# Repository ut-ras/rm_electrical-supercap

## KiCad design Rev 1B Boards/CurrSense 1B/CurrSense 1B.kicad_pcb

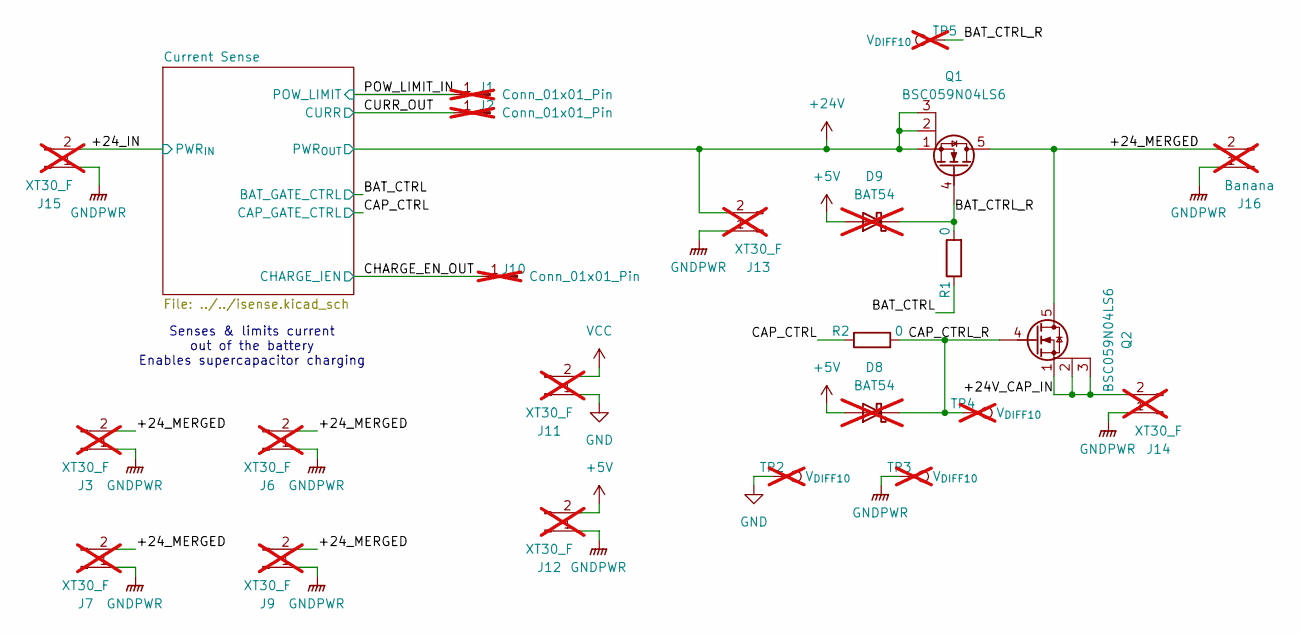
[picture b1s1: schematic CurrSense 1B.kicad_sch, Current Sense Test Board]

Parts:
D8, D9: BAT54; SOT-23_Handsoldering; Mouser Part Number 241-BAT54_R1_00001; not fitted
J1, J2, J10: Conn_01x01_Pin; SolderWire-2.5sqmm_1x01_D2.4mm_OD3.6mm; not fitted
J3, J6, J7, J9, J11, J12, J13, J14, J15: XT30_F; AMASS_XT30U-F_1x02_P5.0mm_Vertical; not fitted
J16: Banana; RM_Banana_Jack_2Pin; not fitted
Q1, Q2: BSC059N04LS6; Infineon_PG-TDSON-8_6.15x5.15mm; Mouser Part Number 726-BSC059N04LS6ATMA
R1, R2: 0; R_0603_1608Metric_Pad0.98x0.95mm_HandSolder; Mouser Part Number 660-RK73Z1JTTDD
TP2, TP3, TP4, TP5: V_{DIFF10}; TestPoint_Bridge_Pitch2.0mm_Drill0.7mm; not fitted

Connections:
+5V: D8.3 (A), D9.3 (A), J12.2
+24V: J13.2, Q1.1 (S), Q1.2 (S), Q1.3 (S); also elsewhere on the board
/+24V_CAP_IN: J14.2, Q2.1 (S), Q2.2 (S), Q2.3 (S)
/+24_IN: J15.2; also elsewhere on the board
/+24_MERGED: J3.2, J6.2, J7.2, J9.2, J16.2, Q1.5 (D), Q2.5 (D)
/BAT_CTRL: R1.1; also elsewhere on the board
/BAT_CTRL_R: D9.1 (K), Q1.4 (G), R1.2, TP5.1
/CAP_CTRL: R2.1; also elsewhere on the board
/CAP_CTRL_R: D8.1 (K), Q2.4 (G), R2.2, TP4.1
/CHARGE_EN_OUT: J10.1; also elsewhere on the board
/CURR_OUT: J2.1; also elsewhere on the board
/POW_LIMIT_IN: J1.1; also elsewhere on the board
GND: J11.1, TP2.1; also elsewhere on the board
GNDPWR: J3.1, J6.1, J7.1, J9.1, J12.1, J13.1, J14.1, J15.1, J16.1, TP3.1; also elsewhere on the board
VCC: J11.2; also elsewhere on the board

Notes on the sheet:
Senses & limits current out of the battery Enables supercapacitor charging

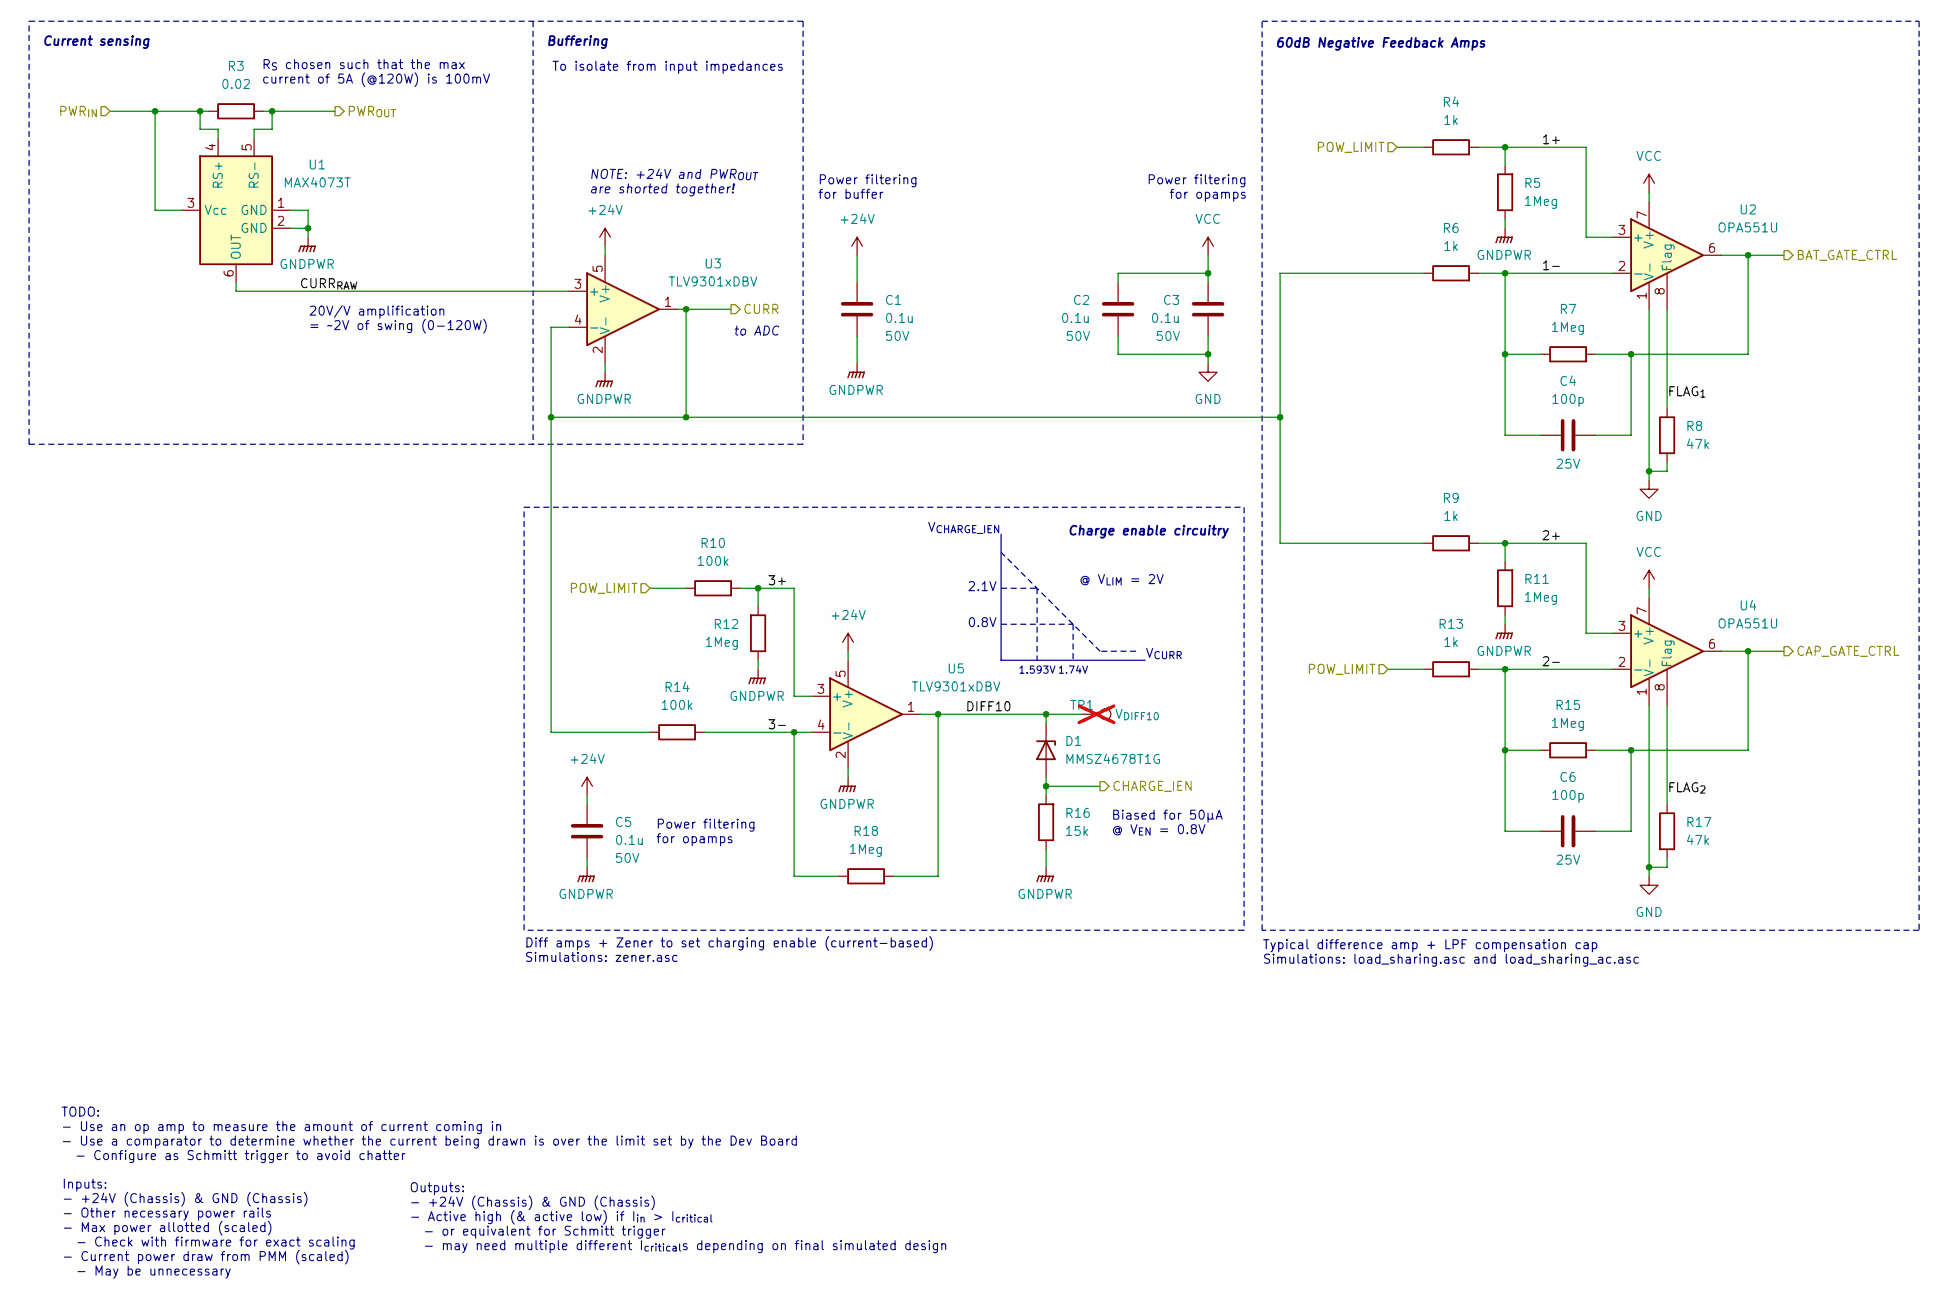
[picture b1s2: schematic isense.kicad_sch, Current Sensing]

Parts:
C1, C2, C3, C5: 0.1u; C_0603_1608Metric_Pad1.08x0.95mm_HandSolder; Voltage Rating 50V; Mouser Part Number 581-KGM15BR71H104JT
C4, C6: 100p; C_0603_1608Metric_Pad1.08x0.95mm_HandSolder; Voltage Rating 25V
D1: MMSZ4678T1G; D_SOD-123; Mouser Part Number 863-MMSZ4678T1G
R3: 0.02; R_0805_2012Metric_Pad1.20x1.40mm_HandSolder; Mouser Part Number 504-MFSA0805R0200FIM
R4, R6, R9, R13: 1k; R_0603_1608Metric_Pad0.98x0.95mm_HandSolder; Mouser Part Number 660-RN73R1JTD1001F50
R5, R7, R11, R12, R15, R18: 1Meg; R_0603_1608Metric_Pad0.98x0.95mm_HandSolder; Mouser Part Number 603-RC0603FR-071MP
R8, R17: 47k; R_0603_1608Metric_Pad0.98x0.95mm_HandSolder; Mouser Part Number 603-RC0603FR-1047KL
R10, R14: 100k; R_0603_1608Metric_Pad0.98x0.95mm_HandSolder; Mouser Part Number 660-RN73H1JTD1003D25
R16: 15k; R_0603_1608Metric_Pad0.98x0.95mm_HandSolder; Mouser Part Number 603-RT0603FRE1315KL
TP1: V_{DIFF10}; TestPoint_Bridge_Pitch2.0mm_Drill0.7mm; not fitted
U1: MAX4073T; SOT-23-6_Handsoldering; Mouser Part Number 700-MAX4073TAUT+T
U2, U4: OPA551U; SOIC-8_3.9x4.9mm_P1.27mm; Mouser Part Number 595-OPA551UA
U3, U5: TLV9301xDBV; SOT-23-5_HandSoldering; Mouser Part Number 595-TLV9301IDBVR

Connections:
+24V: C1.1, C5.1, R3.2, U1.5 (RS-), U3.5 (V+), U5.5 (V+); also elsewhere on the board
/+24_IN: R3.1, U1.3 (Vcc), U1.4 (RS+); also elsewhere on the board
/BAT_CTRL: C4.2, R7.2, U2.6; also elsewhere on the board
/CAP_CTRL: C6.2, R15.2, U4.6; also elsewhere on the board
/CHARGE_EN_OUT: D1.2 (A), R16.2; also elsewhere on the board
/CURR_OUT: R6.1, R9.1, R14.1, U3.1, U3.4 (-); also elsewhere on the board
/Current Sense/1+: R4.2, R5.2, U2.3 (+)
/Current Sense/1-: C4.1, R6.2, R7.1, U2.2 (-); also elsewhere on the board
/Current Sense/2+: R9.2, R11.2, U4.3 (+)
/Current Sense/2-: C6.1, R13.2, R15.1, U4.2 (-); also elsewhere on the board
/Current Sense/3+: R10.2, R12.2, U5.3 (+)
/Current Sense/3-: R14.2, R18.1, U5.4 (-); also elsewhere on the board
/Current Sense/CURR_{RAW}: U1.6 (OUT), U3.3 (+); also elsewhere on the board
/Current Sense/DIFF10: D1.1 (K), R18.2, TP1.1, U5.1; also elsewhere on the board
/Current Sense/FLAG_{1}: R8.1, U2.8 (Flag)
/Current Sense/FLAG_{2}: R17.1, U4.8 (Flag)
/POW_LIMIT_IN: R4.1, R10.1, R13.1; also elsewhere on the board
GND: C2.2, C3.2, R8.2, R17.2, U2.1 (V-), U2.4 (V-), U2.5 (V-), U4.1 (V-), U4.4 (V-), U4.5 (V-); also elsewhere on the board
GNDPWR: C1.2, C5.2, R5.1, R11.1, R12.1, R16.1, U1.1 (GND), U1.2 (GND), U3.2 (V-), U5.2 (V-); also elsewhere on the board
VCC: C2.1, C3.1, U2.7 (V+), U4.7 (V+); also elsewhere on the board

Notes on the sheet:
Inputs: - +24V (Chassis) & GND (Chassis) - Other necessary power rails - Max power allotted (scaled) - Check with firmware for exact scaling - Current power draw from PMM (scaled) - May be unnecessary
Power filtering for buffer
Power filtering for opamps
1.593V
Biased for 50µA @ V_{EN} = 0.8V
60dB Negative Feedback Amps
0.8V
1.74V
20V/V amplification = ~2V of swing (0-120W)
Typical difference amp + LPF compensation cap Simulations: load_sharing.asc and load_sharing_ac.asc
Diff amps + Zener to set charging enable (current-based) Simulations: zener.asc
Outputs: - +24V (Chassis) & GND (Chassis) - Active high (& active low) if I_{in} > I_{critical} - or equivalent for Schmitt trigger - may need multiple different I_{critical}s depending on final simulated design
V_{CHARGE_IEN}
V_{CURR}
R_{S} chosen such that the max current of 5A (@120W) is 100mV
TODO: - Use an op amp to measure the amount of current coming in - Use a comparator to determine whether the current being drawn is over the limit set by the Dev Board - Configure as Schmitt trigger to avoid chatter
2.1V
NOTE: +24V and PWR_{OUT} are shorted together!
To isolate from input impedances
Charge enable circuitry
to ADC
Buffering
Current sensing
@ V_{LIM} = 2V

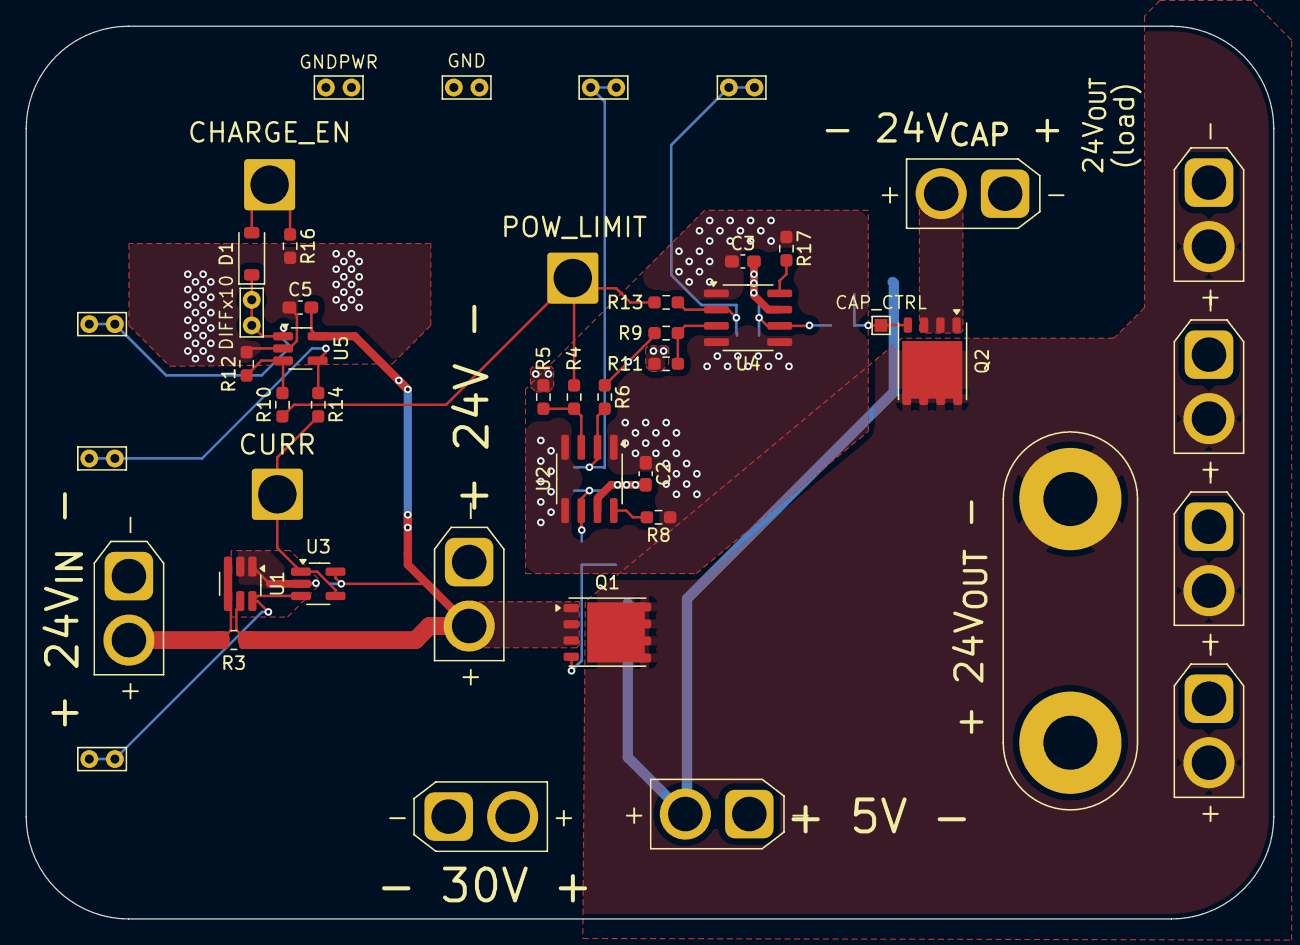
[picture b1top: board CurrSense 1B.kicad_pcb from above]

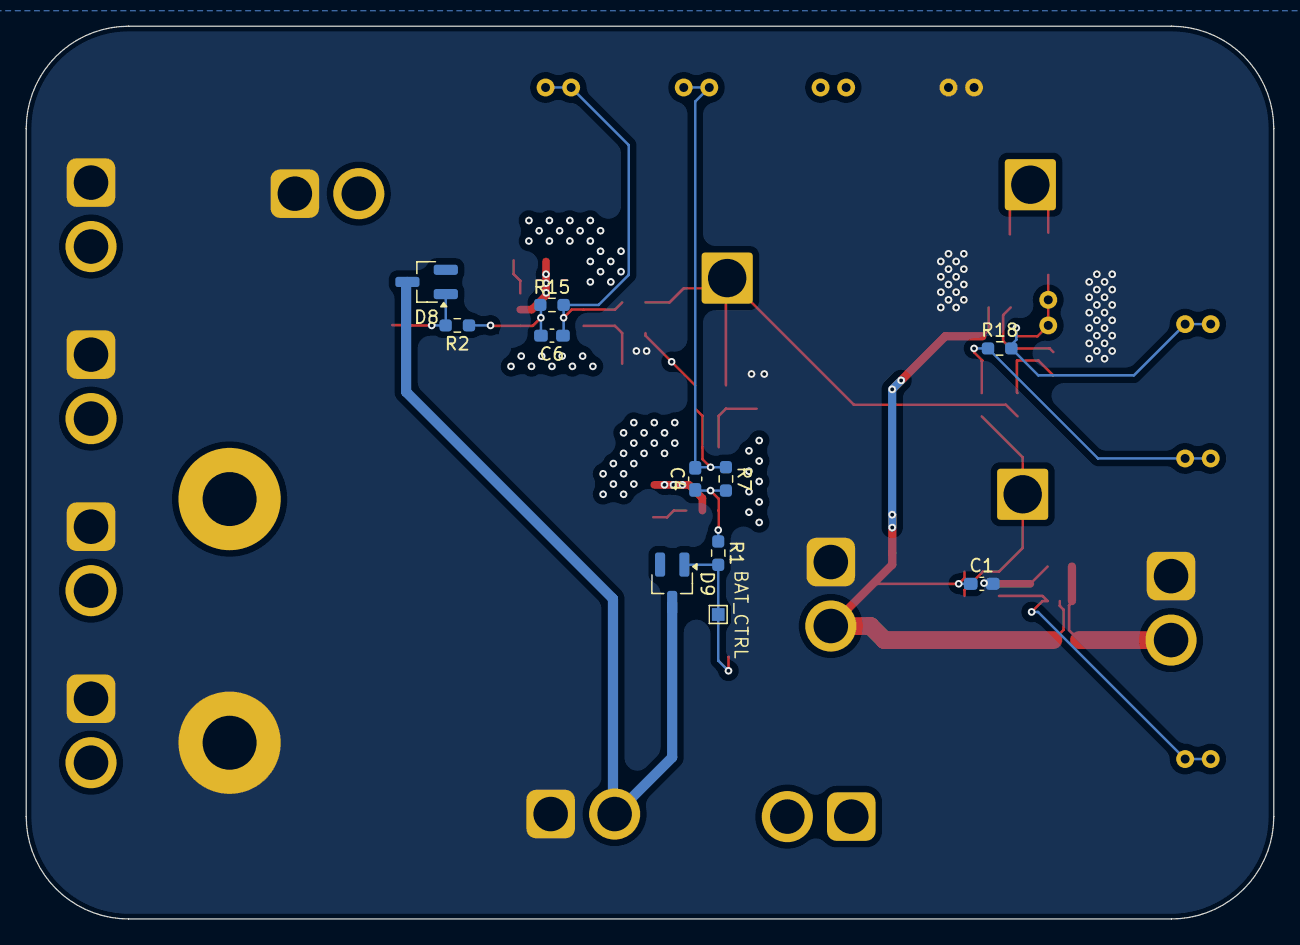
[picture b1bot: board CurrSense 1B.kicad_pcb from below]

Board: 4 copper layers, 97.5 x 69.8 mm, 57 parts (11 on the bottom side), 25 nets.

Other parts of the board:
TP6: CE_OUT; TestPoint_Bridge_Pitch2.0mm_Drill0.7mm
TP7: CE_IN_NEG; TestPoint_Bridge_Pitch2.0mm_Drill0.7mm
TP8: I_OUT; TestPoint_Bridge_Pitch2.0mm_Drill0.7mm
TP9: CAP_IN_NEG; TestPoint_Bridge_Pitch2.0mm_Drill0.7mm
TP10: BAT_IN_NEG; TestPoint_Bridge_Pitch2.0mm_Drill0.7mm

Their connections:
/Current Sense/1-: TP10.1; also elsewhere on the board
/Current Sense/2-: TP9.1; also elsewhere on the board
/Current Sense/3-: TP7.1; also elsewhere on the board
/Current Sense/CURR_{RAW}: TP8.1; also elsewhere on the board
/Current Sense/DIFF10: TP6.1; also elsewhere on the board

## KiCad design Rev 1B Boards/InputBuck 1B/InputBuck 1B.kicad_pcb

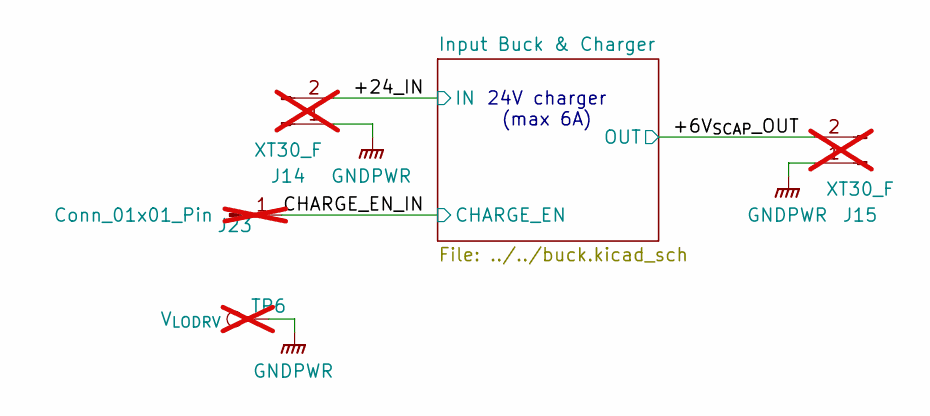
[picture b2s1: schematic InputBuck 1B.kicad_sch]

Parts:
J14, J15: XT30_F; AMASS_XT30U-F_1x02_P5.0mm_Vertical; not fitted
J23: Conn_01x01_Pin; SolderWire-2.5sqmm_1x01_D2.4mm_OD3.6mm; not fitted
TP6: V_{LODRV}; TestPoint_Bridge_Pitch2.0mm_Drill0.7mm; not fitted

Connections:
/+6V_{SCAP}_OUT: J15.2; also elsewhere on the board
/+24_IN: J14.2; also elsewhere on the board
/CHARGE_EN_IN: J23.1; also elsewhere on the board
GNDPWR: J14.1, J15.1, TP6.1; also elsewhere on the board

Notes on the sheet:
24V charger (max 6A)

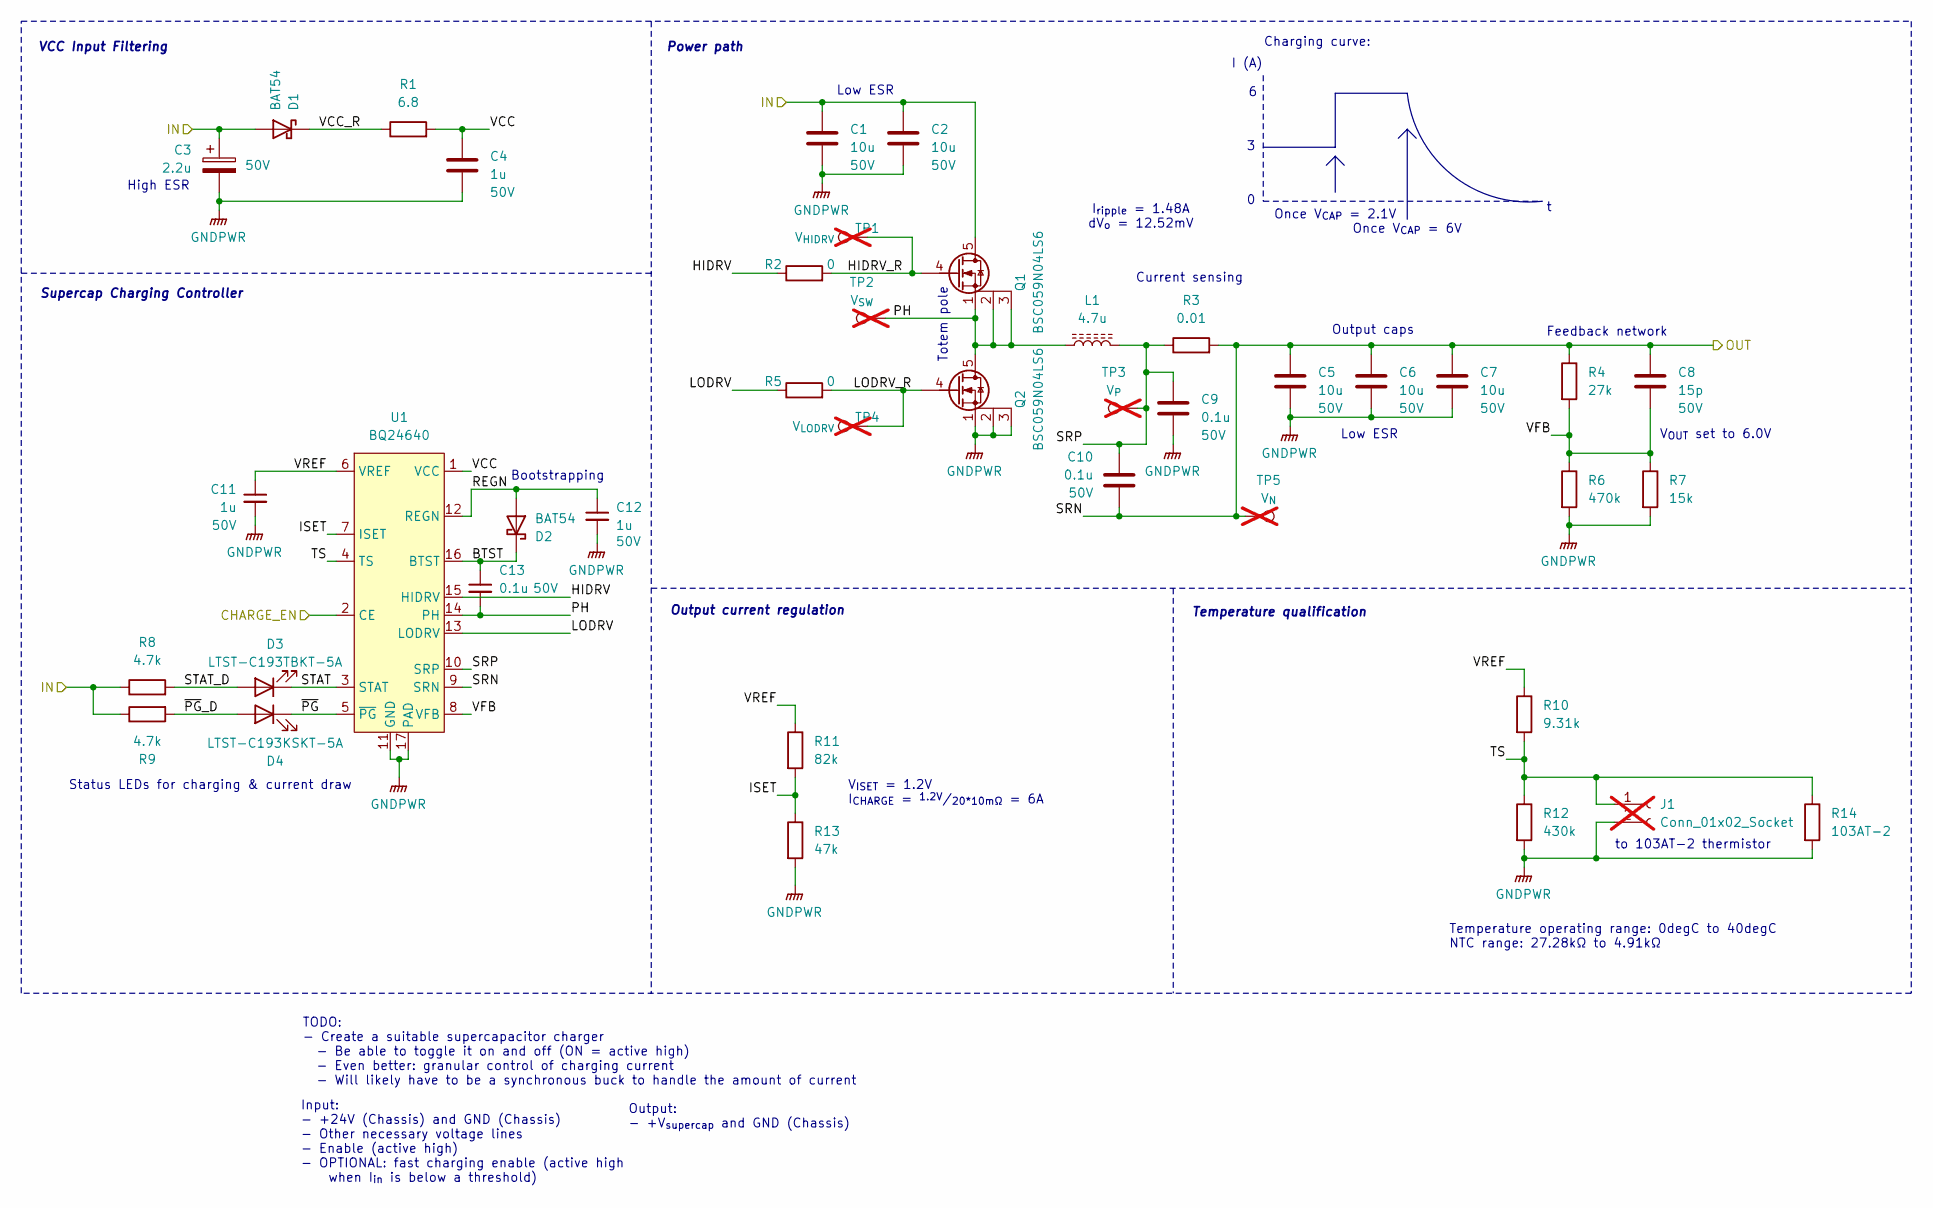
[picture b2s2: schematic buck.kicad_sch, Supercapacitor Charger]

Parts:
C1, C2, C5, C6, C7: 10u; C_1206_3216Metric_Pad1.33x1.80mm_HandSolder; Voltage Rating 50V; Mouser Part Number 187-CL31A106KBHNNNE
C3: 2.2u; C_Radial_D5.0mm_H11.0mm_P2.00mm; Voltage Rating 50V; Mouser Part Number 710-860010672006
C4, C11, C12: 1u; C_0603_1608Metric_Pad1.08x0.95mm_HandSolder; Voltage Rating 50V; Mouser Part Number 963-UMK107BJ105KA-T
C8: 15p; C_0603_1608Metric_Pad1.08x0.95mm_HandSolder; Voltage Rating 50V; Mouser Part Number 791-0603N150F500CT
C9, C10, C13: 0.1u; C_0603_1608Metric_Pad1.08x0.95mm_HandSolder; Voltage Rating 50V; Mouser Part Number 581-KGM15BR71H104JT
D1, D2: BAT54; SOT-23_Handsoldering; Mouser Part Number 241-BAT54_R1_00001
D3: LTST-C193TBKT-5A; LED_0603_1608Metric_Pad1.05x0.95mm_HandSolder; Mouser Part Number 859-LTSTC193TBKT5A
D4: LTST-C193KSKT-5A; LED_0603_1608Metric_Pad1.05x0.95mm_HandSolder; Mouser Part Number 859-LTSTC193KSKT5A
J1: Conn_01x02_Socket; PinSocket_1x02_P2.54mm_Vertical; not fitted
L1: 4.7u; L_Bourns_SRN8040TA; Mouser Part Number 652-SRN8040TA-4R7M
Q1, Q2: BSC059N04LS6; Infineon_PG-TDSON-8_6.15x5.15mm; Mouser Part Number 726-BSC059N04LS6ATMA
R1: 6.8; R_0805_2012Metric_Pad1.20x1.40mm_HandSolder; Mouser Part Number 660-RK73B2ATTD6R8J
R2, R5: 0; R_0603_1608Metric_Pad0.98x0.95mm_HandSolder; Mouser Part Number 660-RK73Z1JTTDD
R3: 0.01; R_0612_1632Metric_Pad1.18x3.40mm_HandSolder; Mouser Part Number 652-CFG0612FXR010ELF
R4: 27k; R_0603_1608Metric_Pad0.98x0.95mm_HandSolder; Mouser Part Number 660-RN73H1JTD2702B25
R6: 470k; R_0603_1608Metric_Pad0.98x0.95mm_HandSolder; Mouser Part Number 660-RN73R1JTD4703B25
R7: 15k; R_0603_1608Metric_Pad0.98x0.95mm_HandSolder; Mouser Part Number 603-RT0603FRE1315KL
R8, R9: 4.7k; R_0603_1608Metric_Pad0.98x0.95mm_HandSolder; Mouser Part Number 660-RN73R1JTD4701F50
R10: 9.31k; R_0603_1608Metric_Pad0.98x0.95mm_HandSolder; Mouser Part Number 603-RT0603DRE079K31L
R11: 82k; R_0603_1608Metric_Pad0.98x0.95mm_HandSolder; Mouser Part Number 603-RT0603FRE0782KL
R12: 430k; R_0603_1608Metric_Pad0.98x0.95mm_HandSolder; Mouser Part Number 603-RT0603FRE07430KL
R13: 47k; R_0603_1608Metric_Pad0.98x0.95mm_HandSolder; Mouser Part Number 603-RC0603FR-1047KL
R14: 103AT-2; Mouser Part Number 504-NRNE104H3435B2H
TP1: V_{HIDRV}; TestPoint_Bridge_Pitch2.0mm_Drill0.7mm; not fitted
TP2: V_{SW}; TestPoint_Bridge_Pitch2.0mm_Drill0.7mm; not fitted
TP3: V_{P}; TestPoint_Bridge_Pitch2.0mm_Drill0.7mm; not fitted
TP4: V_{LODRV}; TestPoint_Bridge_Pitch2.0mm_Drill0.7mm; not fitted
TP5: V_{N}; TestPoint_Bridge_Pitch2.0mm_Drill0.7mm; not fitted
U1: BQ24640; QFN50P350X350X100-17N-D; Mouser Part Number 595-BQ24640RVAR

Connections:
/+6V_{SCAP}_OUT: C5.1, C6.1, C7.1, C8.1, C10.2, R3.2, R4.1, TP5.1, U1.9 (SRN); also elsewhere on the board
/+24_IN: C1.1, C2.1, C3.1, D1.1 (A), Q1.5 (D), R8.1, R9.1; also elsewhere on the board
/CHARGE_EN_IN: U1.2 (CE); also elsewhere on the board
/Input Buck & Charger/BTST: C13.1, D2.3 (K), U1.16 (BTST)
/Input Buck & Charger/HIDRV: R2.1, U1.15 (HIDRV)
/Input Buck & Charger/HIDRV_R: Q1.4 (G), R2.2, TP1.1
/Input Buck & Charger/ISET: R11.2, R13.1, U1.7 (ISET)
/Input Buck & Charger/LODRV: R5.1, U1.13 (LODRV)
/Input Buck & Charger/LODRV_R: Q2.4 (G), R5.2, TP4.1
/Input Buck & Charger/PH: C13.2, L1.1, Q1.1 (S), Q1.2 (S), Q1.3 (S), Q2.5 (D), TP2.1, U1.14 (PH)
/Input Buck & Charger/REGN: C12.1, D2.1 (A), U1.12 (REGN)
/Input Buck & Charger/SRP: C9.1, C10.1, L1.2, R3.1, TP3.1, U1.10 (SRP)
/Input Buck & Charger/STAT: D3.1 (K), U1.3 (STAT)
/Input Buck & Charger/STAT_D: D3.2 (A), R8.2
/Input Buck & Charger/TS: J1.1, R10.2, R12.1, U1.4 (TS)
/Input Buck & Charger/VCC: C4.1, R1.2, U1.1 (VCC)
/Input Buck & Charger/VCC_R: D1.3 (K), R1.1
/Input Buck & Charger/VFB: C8.2, R4.2, R6.1, R7.1, U1.8 (VFB)
/Input Buck & Charger/VREF: C11.1, R10.1, R11.1, U1.6 (VREF)
/Input Buck & Charger/~PG: D4.1 (K), U1.5 (~PG)
/Input Buck & Charger/~PG_D: D4.2 (A), R9.2
GNDPWR: C1.2, C2.2, C3.2, C4.2, C5.2, C6.2, C7.2, C9.2, C11.2, C12.2, J1.2, Q2.1 (S), Q2.2 (S), Q2.3 (S), R6.2, R7.2, R12.2, R13.2, U1.11 (GND), U1.17 (PAD); also elsewhere on the board

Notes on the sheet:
Charging curve:
Current sensing
Once V_{CAP} = 6V
Totem pole
to 103AT-2 thermistor
TODO: - Create a suitable supercapacitor charger - Be able to toggle it on and off (ON = active high) - Even better: granular control of charging current - Will likely have to be a synchronous buck to handle the amount of current
Status LEDs for charging & current draw
Low ESR
V_{OUT} set to 6.0V
Temperature qualification
I_{ripple} = 1.48A dV_{o} = 12.52mV
Output caps
Bootstrapping
V_{ISET} = 1.2V I_{CHARGE} = ^{1.2V}/_{20*10mΩ} = 6A
Once V_{CAP} = 2.1V
Input: - +24V (Chassis) and GND (Chassis) - Other necessary voltage lines - Enable (active high) - OPTIONAL: fast charging enable (active high when I_{in} is below a threshold)
High ESR
Feedback network
Output: - +V_{supercap} and GND (Chassis)
Power path
Supercap Charging Controller
VCC Input Filtering
Temperature operating range: 0degC to 40degC NTC range: 27.28kΩ to 4.91kΩ
I (A)
Output current regulation

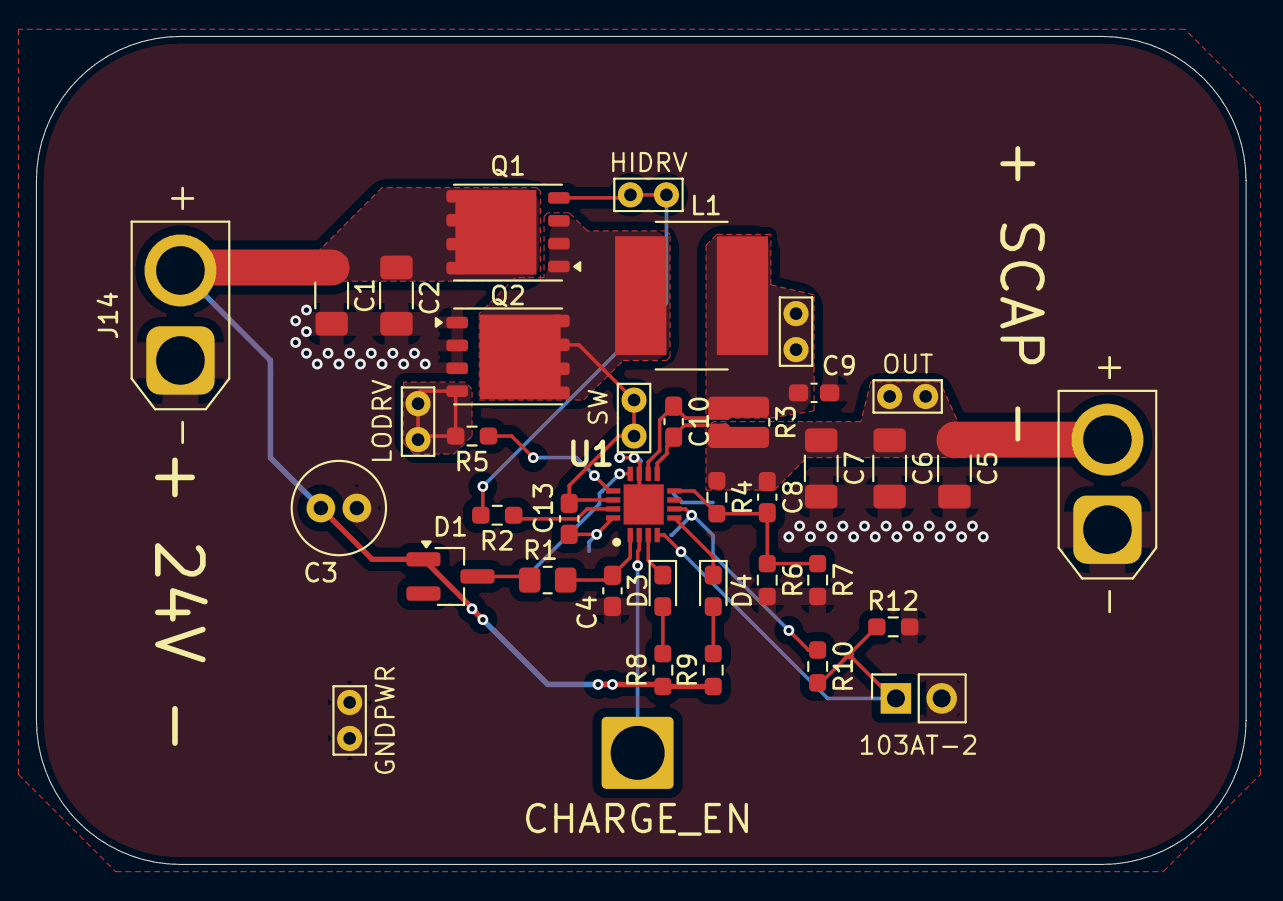
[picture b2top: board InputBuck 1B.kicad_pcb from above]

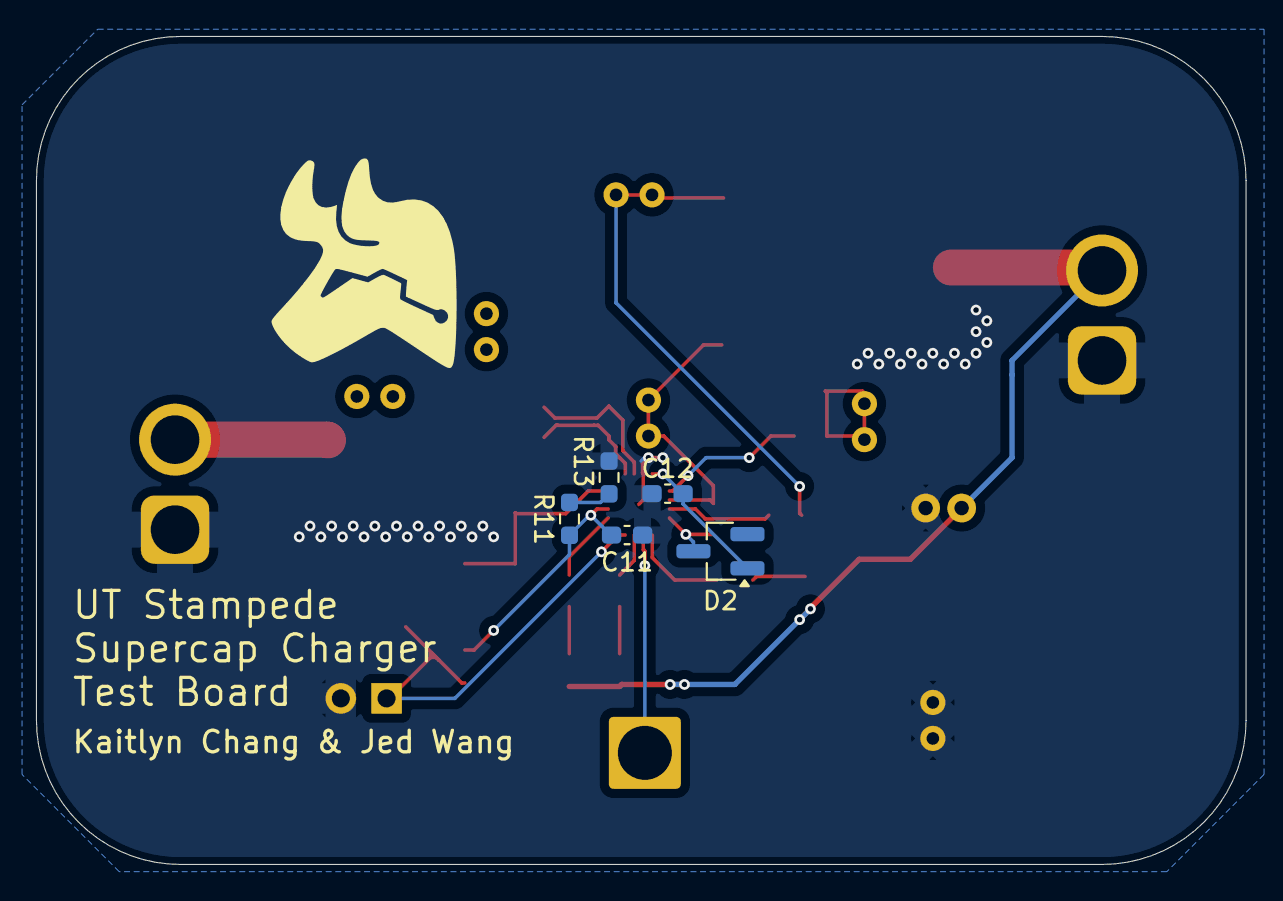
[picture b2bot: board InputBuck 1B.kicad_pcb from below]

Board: 4 copper layers, 67.2 x 46.0 mm, 44 parts (5 on the bottom side), 22 nets.

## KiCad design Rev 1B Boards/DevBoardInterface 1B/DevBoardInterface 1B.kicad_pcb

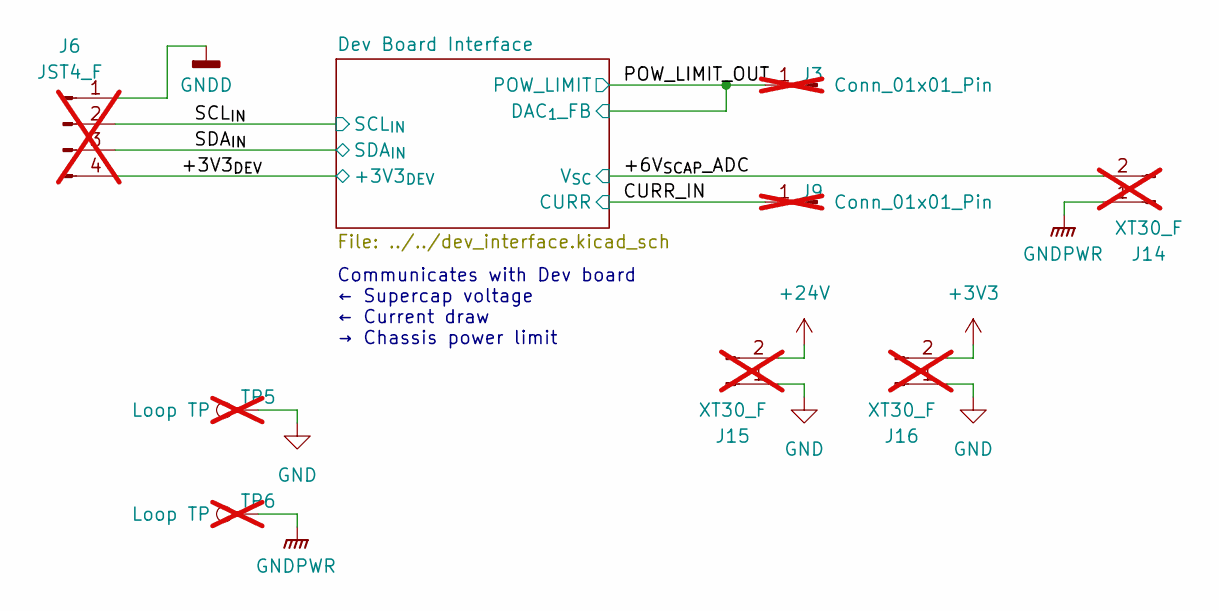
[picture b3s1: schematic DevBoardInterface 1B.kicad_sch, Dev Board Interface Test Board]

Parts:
J3, J9: Conn_01x01_Pin; SolderWire-2.5sqmm_1x01_D2.4mm_OD3.6mm; not fitted
J6: JST4_F; JST_GH_BM04B-GHS-TBT_1x04-1MP_P1.25mm_Vertical; not fitted
J14, J15, J16: XT30_F; AMASS_XT30U-F_1x02_P5.0mm_Vertical; not fitted
TP5, TP6: Loop TP; TestPoint_Bridge_Pitch2.0mm_Drill0.7mm; not fitted

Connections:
+3V3: J16.2; also elsewhere on the board
+24V: J15.2; also elsewhere on the board
/+3V3_{DEV}: J6.4; also elsewhere on the board
/+6V_{SCAP}_ADC: J14.2; also elsewhere on the board
/CURR_IN: J9.1; also elsewhere on the board
/POW_LIMIT_OUT: J3.1; also elsewhere on the board
/SCL_{IN}: J6.2; also elsewhere on the board
/SDA_{IN}: J6.3; also elsewhere on the board
GND: J15.1, J16.1, TP5.1; also elsewhere on the board
GNDD: J6.1; also elsewhere on the board
GNDPWR: J14.1, TP6.1; also elsewhere on the board

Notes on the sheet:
Communicates with Dev board ← Supercap voltage ← Current draw → Chassis power limit

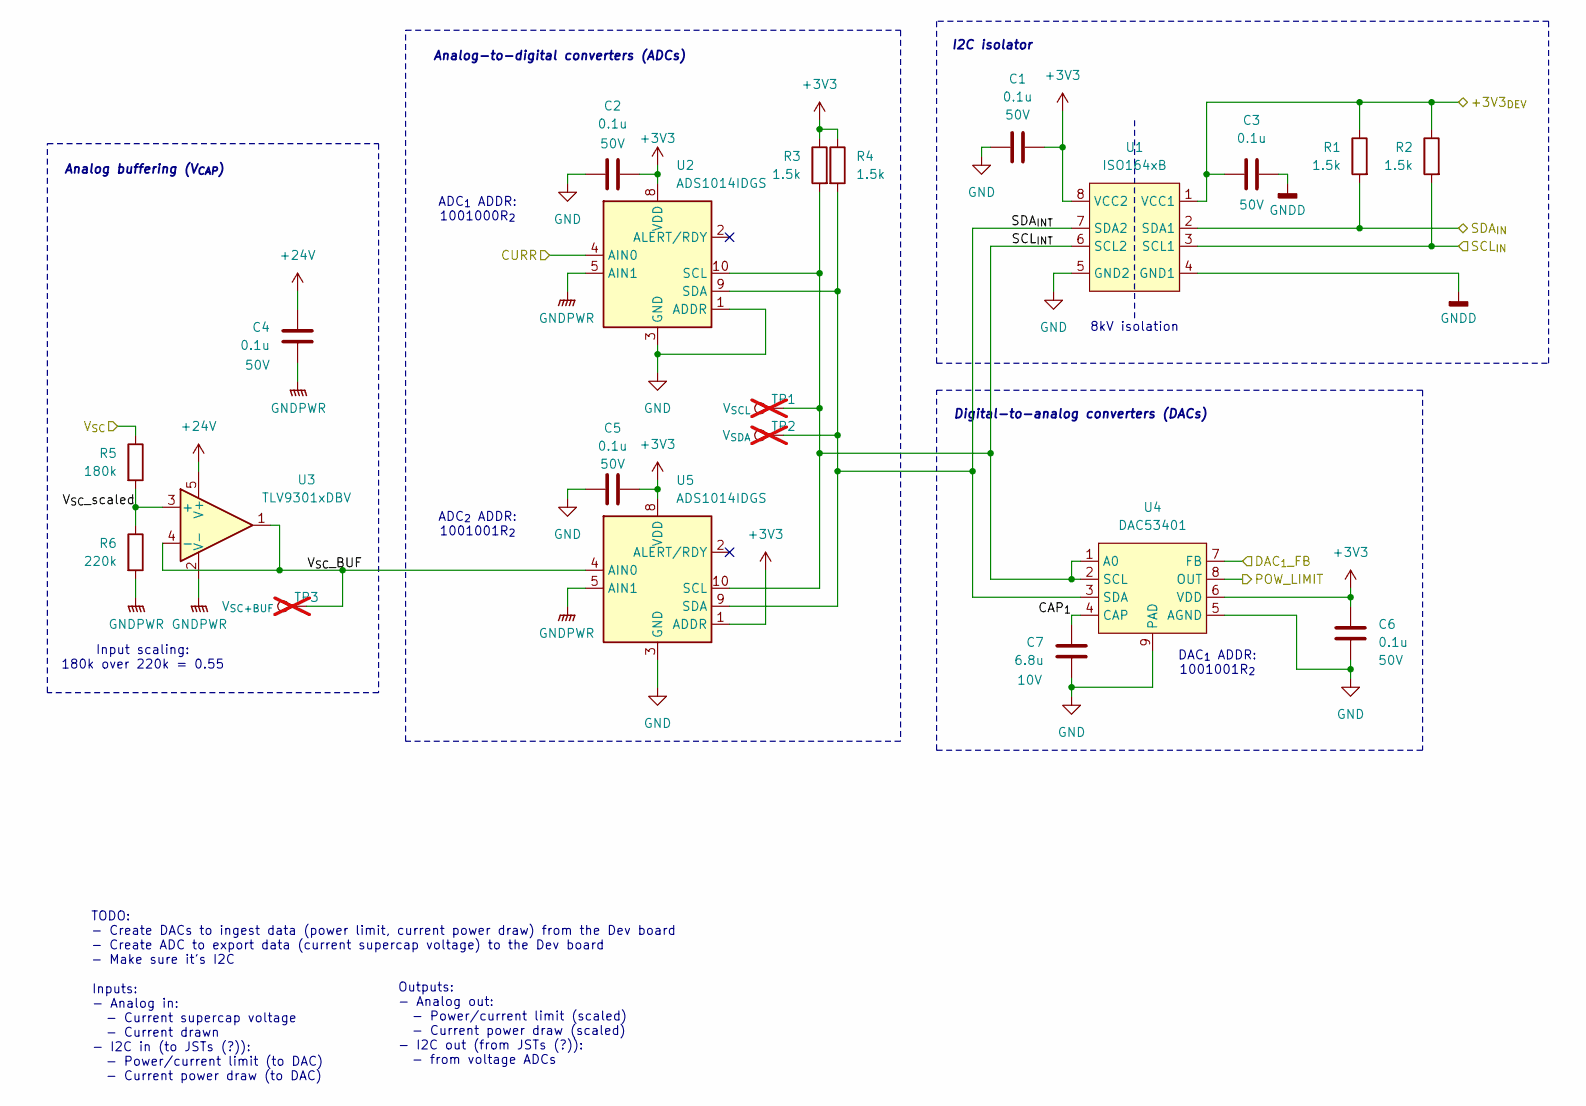
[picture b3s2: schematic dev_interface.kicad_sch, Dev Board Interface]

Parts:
C1, C2, C3, C4, C5, C6: 0.1u; C_0603_1608Metric_Pad1.08x0.95mm_HandSolder; Voltage Rating 50V; Mouser Part Number 581-KGM15BR71H104JT
C7: 6.8u; C_0603_1608Metric_Pad1.08x0.95mm_HandSolder; Voltage Rating 10V; Mouser Part Number 810-C2012X5R1A685K0C
R1, R2, R3, R4: 1.5k; R_0603_1608Metric_Pad0.98x0.95mm_HandSolder; Mouser Part Number 603-RC0603FR-7W1K5L
R5: 180k; R_0603_1608Metric_Pad0.98x0.95mm_HandSolder; Mouser Part Number 603-RT0603DRE07180KL
R6: 220k; R_0603_1608Metric_Pad0.98x0.95mm_HandSolder; Mouser Part Number 660-RK73H1JTTD2203F
TP1: V_{SCL}; TestPoint_Bridge_Pitch2.0mm_Drill0.7mm; not fitted
TP2: V_{SDA}; TestPoint_Bridge_Pitch2.0mm_Drill0.7mm; not fitted
TP3: V_{SC+BUF}; TestPoint_Bridge_Pitch2.0mm_Drill0.7mm; not fitted
U1: ISO164xB; SOIC-8_3.9x4.9mm_P1.27mm; Mouser Part Number 595-ISO1641BDR
U2, U5: ADS1014IDGS; TSSOP-10_3x3mm_P0.5mm; Mouser Part Number 595-ADS1014IDGSR
U3: TLV9301xDBV; SOT-23-5_HandSoldering; Mouser Part Number 595-TLV9301IDBVR
U4: DAC53401; WSON-8-1EP_2x2mm_P0.5mm_EP0.9x1.6mm; Mouser Part Number 595-DAC53401DSGR

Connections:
+3V3: C1.1, C2.2, C5.2, C6.2, R3.1, R4.1, U1.8 (VCC2), U2.8 (VDD), U4.6 (VDD), U5.1 (ADDR), U5.8 (VDD); also elsewhere on the board
+24V: C4.2, U3.5 (V+); also elsewhere on the board
/+3V3_{DEV}: C3.2, R1.1, R2.1, U1.1 (VCC1); also elsewhere on the board
/+6V_{SCAP}_ADC: R5.1; also elsewhere on the board
/CURR_IN: U2.4 (AIN0); also elsewhere on the board
/Dev Board Interface/CAP_{1}: C7.1, U4.4 (CAP)
/Dev Board Interface/SCL_{INT}: R3.2, TP1.1, U1.6 (SCL2), U2.10 (SCL), U4.1 (A0), U4.2 (SCL), U5.10 (SCL)
/Dev Board Interface/SDA_{INT}: R4.2, TP2.1, U1.7 (SDA2), U2.9 (SDA), U4.3 (SDA), U5.9 (SDA)
/Dev Board Interface/V_{SC}_BUF: TP3.1, U3.1, U3.4 (-), U5.4 (AIN0)
/Dev Board Interface/V_{SC}_scaled: R5.2, R6.1, U3.3 (+)
/POW_LIMIT_OUT: U4.7 (FB), U4.8 (OUT); also elsewhere on the board
/SCL_{IN}: R2.2, U1.3 (SCL1); also elsewhere on the board
/SDA_{IN}: R1.2, U1.2 (SDA1); also elsewhere on the board
GND: C1.2, C2.1, C5.1, C6.1, C7.2, U1.5 (GND2), U2.1 (ADDR), U2.3 (GND), U4.5 (AGND), U4.9 (PAD), U5.3 (GND); also elsewhere on the board
GNDD: C3.1, U1.4 (GND1); also elsewhere on the board
GNDPWR: C4.1, R6.2, U2.5 (AIN1), U3.2 (V-), U5.5 (AIN1); also elsewhere on the board

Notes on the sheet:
Input scaling: 180k over 220k = 0.55
I2C isolator
TODO: - Create DACs to ingest data (power limit, current power draw) from the Dev board - Create ADC to export data (current supercap voltage) to the Dev board - Make sure it's I2C
Inputs: - Analog in: - Current supercap voltage - Current drawn - I2C in (to JSTs (?)): - Power/current limit (to DAC) - Current power draw (to DAC)
ADC_{2} ADDR: 1001001R_{2}
Outputs: - Analog out: - Power/current limit (scaled) - Current power draw (scaled) - I2C out (from JSTs (?)): - from voltage ADCs
Digital-to-analog converters (DACs)
DAC_{1} ADDR: 1001001R_{2}
Analog-to-digital converters (ADCs)
8kV isolation
Analog buffering (V_{CAP})
ADC_{1} ADDR: 1001000R_{2}
